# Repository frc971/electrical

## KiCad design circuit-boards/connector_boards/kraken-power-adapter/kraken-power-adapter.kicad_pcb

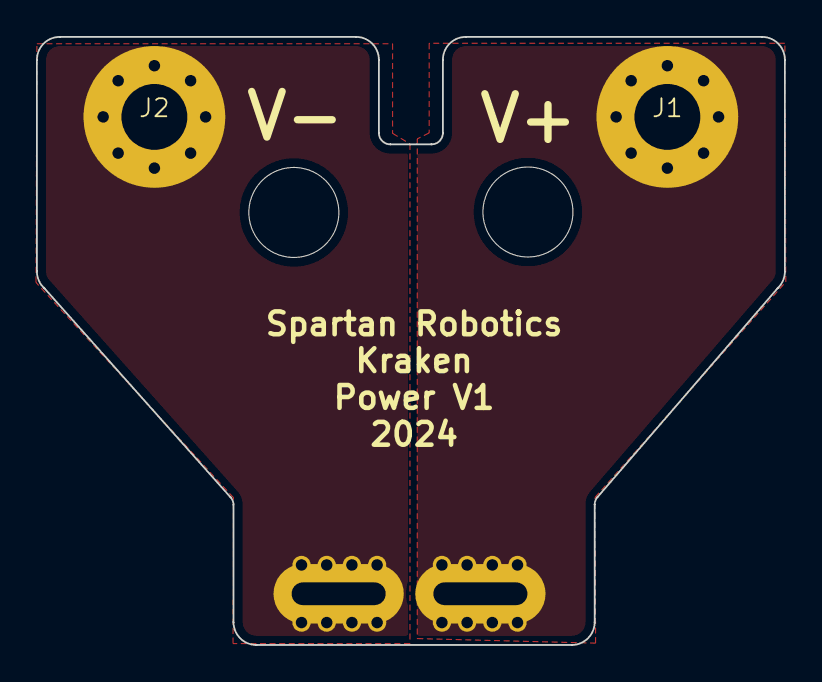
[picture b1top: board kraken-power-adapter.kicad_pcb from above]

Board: 4 copper layers, 41.6 x 33.8 mm, 5 parts (1 on the bottom side), 2 nets.

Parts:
H1, H2: CAN Screw Clearance Hole; MountingHole_5mm
J1: Vbat+; ScrewTerminal-#6
J2: Vbat-; ScrewTerminal-#6
J3: Vbat PP15-45; Dual-side-by-side-1335G1

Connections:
/Vbat+: J1.1, J3.2
/Vbat-: J2.1, J3.1

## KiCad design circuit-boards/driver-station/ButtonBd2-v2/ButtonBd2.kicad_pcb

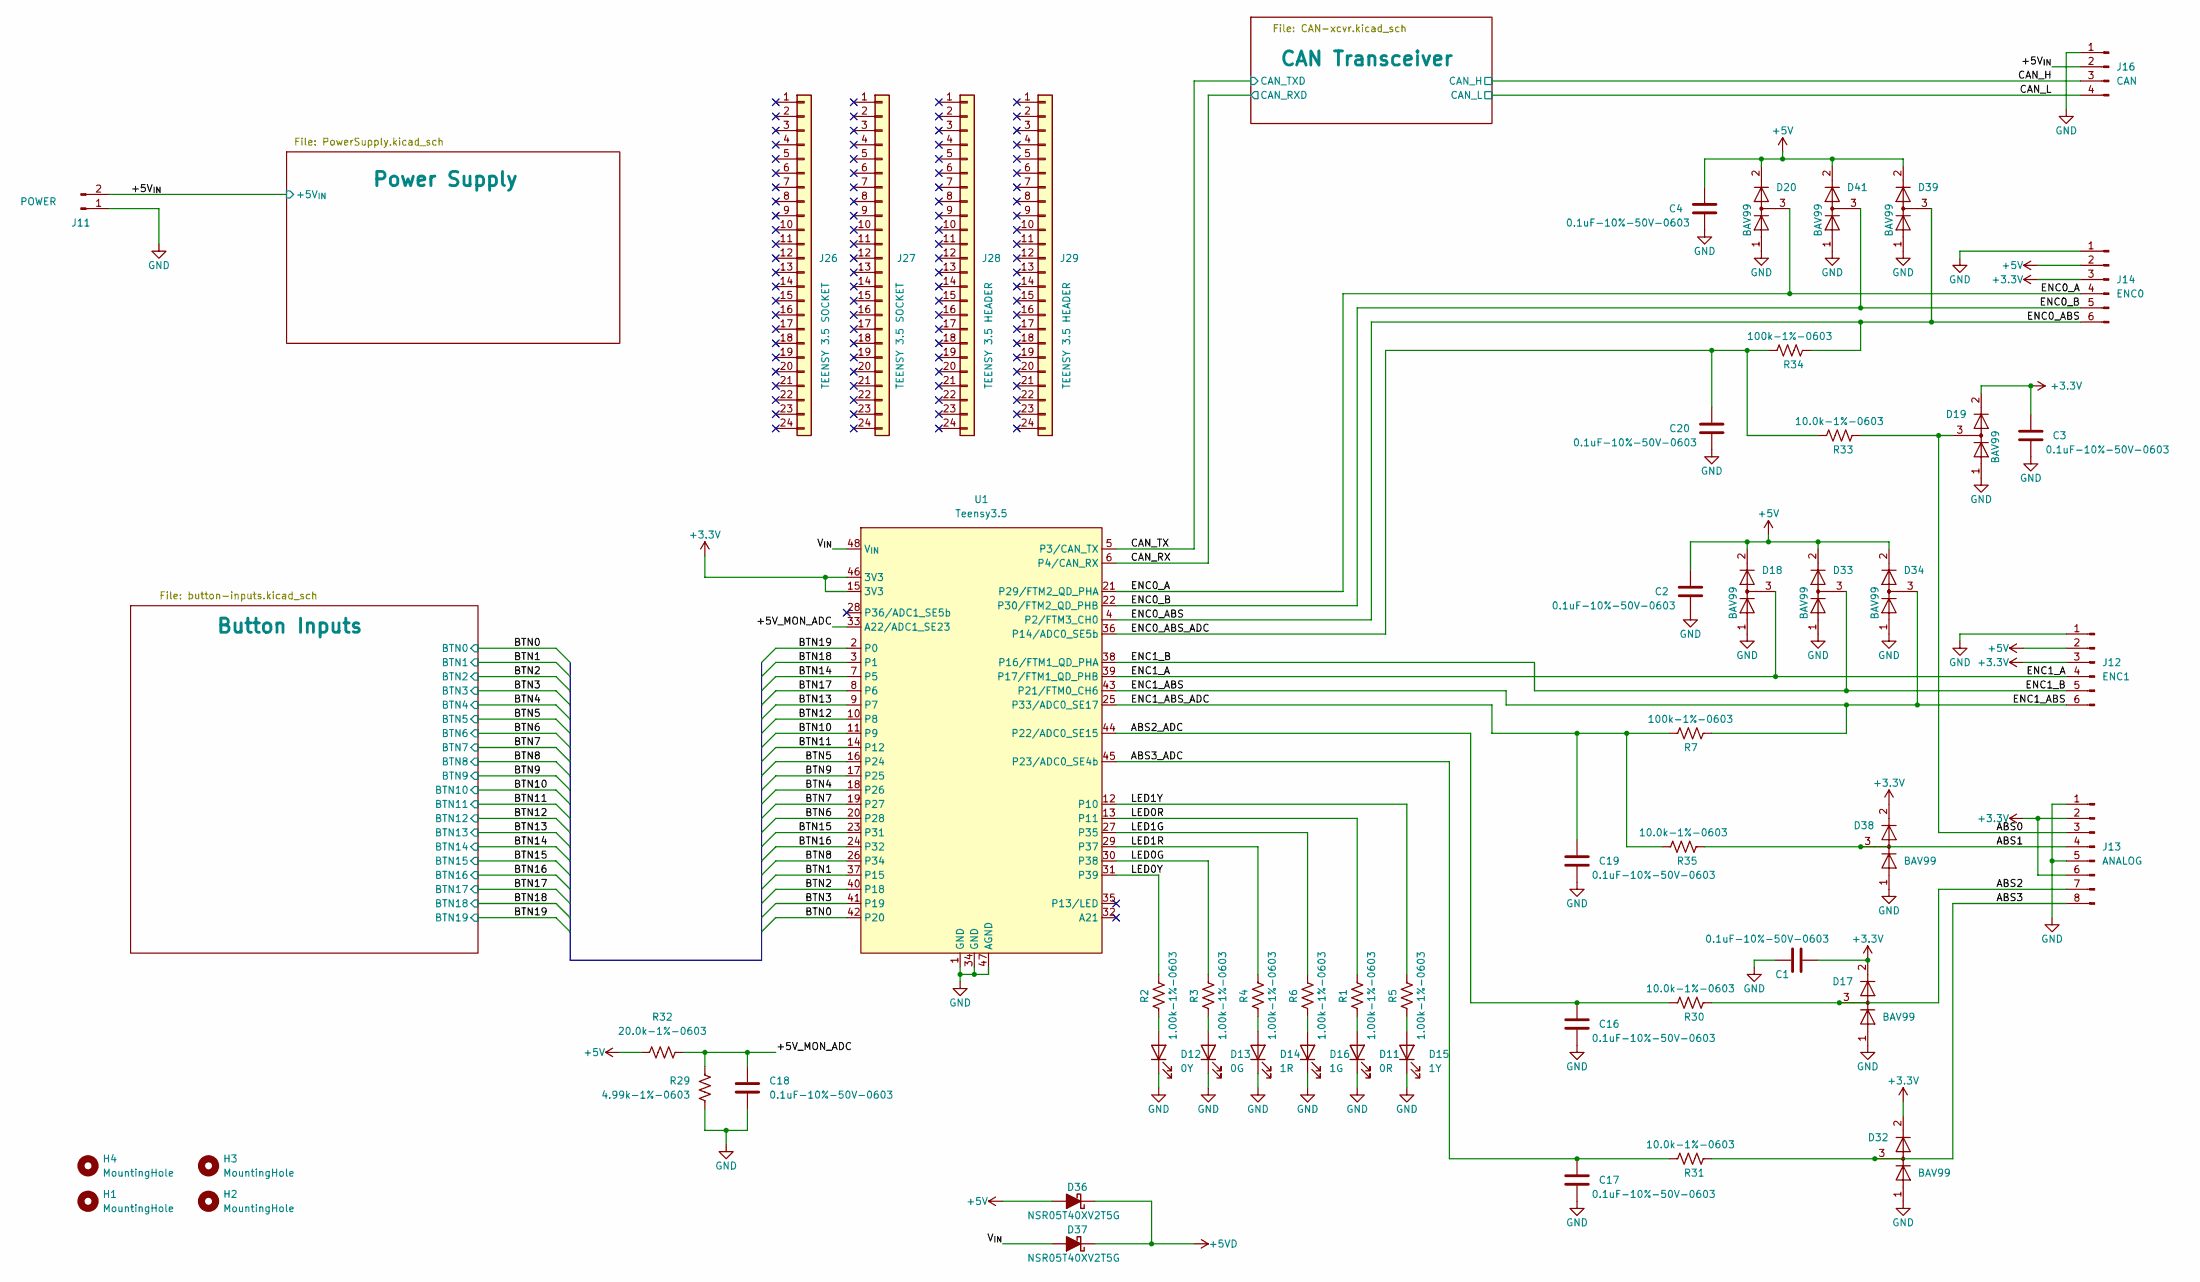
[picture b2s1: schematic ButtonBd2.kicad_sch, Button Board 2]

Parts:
C1, C2, C3, C4, C16, C17, C18, C19, C20: 0.1uF-10%-50V-0603; C_0603_1608Metric; MFG P/N CL10B104KB8NNNC
D11: 0R; LED_0603_1608Metric; MFG P/N 150060RS75000
D12: 0Y; LED_0603_1608Metric; MFG P/N 150060YS75000
D13: 0G; LED_0603_1608Metric; MFG P/N 150060GS75000
D14: 1R; LED_0603_1608Metric; MFG P/N 150060RS75000
D15: 1Y; LED_0603_1608Metric; MFG P/N 150060YS75000
D16: 1G; LED_0603_1608Metric; MFG P/N 150060GS75000
D17, D18, D19, D20, D32, D33, D34, D38, D39, D41: BAV99; SOT-23; MFG P/N BAV99,235
D36, D37: NSR05T40XV2T5G; D_SOD-523; MFG P/N BAT54KFILM
H1, H2, H3, H4: MountingHole; MountingHole_3.2mm_M3
J11: POWER; 70543-0001; MFG P/N 0705430001
J12: ENC1; 70543-0005; MFG P/N 0705430005
J13: ANALOG; 70543-0007; MFG P/N 0705430007
J14: ENC0; 70543-0005; MFG P/N 0705430005
J16: CAN; 70543-0003; MFG P/N 0705430003
J26, J27: TEENSY 3.5 SOCKET; MFG P/N PPPC241LFBN-RC
J28, J29: TEENSY 3.5 HEADER; MFG P/N 0022284245
R1, R2, R3, R4, R5, R6: 1.00k-1%-0603; R_0603_1608Metric; MFG P/N RNCP0603FTD1K00
R7, R34: 100k-1%-0603; R_0603_1608Metric; MFG P/N RC0603FR-07100KL
R29: 4.99k-1%-0603; R_0603_1608Metric; MFG P/N RMCF0603FT4K99
R30, R31, R33, R35: 10.0k-1%-0603; R_0603_1608Metric; MFG P/N RC0603FR-0710KL
R32: 20.0k-1%-0603; R_0603_1608Metric; MFG P/N RC0603FR-0720KL
U1: Teensy3.5; Teensy-DIP-49_W15.24mm_Socket; MFG P/N TEENSY 3.5

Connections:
+3.3V: C1.2, C3.1, D17.2 (A), D19.2 (A), D32.2 (A), D38.2 (A), J12.3, J13.2, J13.6, J14.3, U1.15 (3V3), U1.46 (3V3); also elsewhere on the board
+5V: C2.1, C4.1, D18.2 (A), D20.2 (A), D33.2 (A), D34.2 (A), D36.2 (A), D39.2 (A), D41.2 (A), J12.2, J14.2, R32.2; also elsewhere on the board
+5VD: D36.1 (K), D37.1 (K); also elsewhere on the board
/+5V_MON_ADC: C18.1, R29.1, R32.1, U1.33 (A22/ADC1_SE23)
/+5V_{IN}: J11.2, J16.2; also elsewhere on the board
/ABS0: D19.3 (K), J13.3, R33.2
/ABS1: D38.3 (K), J13.4, R35.2
/ABS2: D17.3 (K), J13.7, R30.2
/ABS2_ADC: C16.1, R30.1, U1.44 (P22/ADC0_SE15)
/ABS3: D32.3 (K), J13.8, R31.2
/ABS3_ADC: C17.1, R31.1, U1.45 (P23/ADC0_SE4b)
/BTN0: U1.42 (P20); also elsewhere on the board
/BTN1: U1.37 (P15); also elsewhere on the board
/BTN2: U1.40 (P18); also elsewhere on the board
/BTN3: U1.41 (P19); also elsewhere on the board
/BTN4: U1.18 (P26); also elsewhere on the board
/BTN5: U1.16 (P24); also elsewhere on the board
/BTN6: U1.20 (P28); also elsewhere on the board
/BTN7: U1.19 (P27); also elsewhere on the board
/BTN8: U1.26 (P34); also elsewhere on the board
/BTN9: U1.17 (P25); also elsewhere on the board
/BTN10: U1.11 (P9); also elsewhere on the board
/BTN11: U1.14 (P12); also elsewhere on the board
/BTN12: U1.10 (P8); also elsewhere on the board
/BTN13: U1.9 (P7); also elsewhere on the board
/BTN14: U1.7 (P5); also elsewhere on the board
/BTN15: U1.23 (P31); also elsewhere on the board
/BTN16: U1.24 (P32); also elsewhere on the board
/BTN17: U1.8 (P6); also elsewhere on the board
/BTN18: U1.3 (P1); also elsewhere on the board
/BTN19: U1.2 (P0); also elsewhere on the board
/CAN_H: J16.3; also elsewhere on the board
/CAN_L: J16.4; also elsewhere on the board
/CAN_RX: U1.6 (P4/CAN_RX); also elsewhere on the board
/CAN_TX: U1.5 (P3/CAN_TX); also elsewhere on the board
/ENC0_A: D20.3 (K), J14.4, U1.21 (P29/FTM2_QD_PHA)
/ENC0_ABS: D39.3 (K), J14.6, R34.2, U1.4 (P2/FTM3_CH0)
/ENC0_ABS_ADC: C20.1, R33.1, R34.1, U1.36 (P14/ADC0_SE5b)
/ENC0_B: D41.3 (K), J14.5, U1.22 (P30/FTM2_QD_PHB)
/ENC1_A: D18.3 (K), J12.4, U1.39 (P17/FTM1_QD_PHB)
/ENC1_ABS: D34.3 (K), J12.6, R7.2, U1.43 (P21/FTM0_CH6)
/ENC1_ABS_ADC: C19.1, R7.1, R35.1, U1.25 (P33/ADC0_SE17)
/ENC1_B: D33.3 (K), J12.5, U1.38 (P16/FTM1_QD_PHA)
/LED0G: R3.1, U1.30 (P38)
/LED0R: R1.1, U1.13 (P11)
/LED0Y: R2.1, U1.31 (P39)
/LED1G: R6.1, U1.27 (P35)
/LED1R: R4.1, U1.29 (P37)
/LED1Y: R5.1, U1.12 (P10)
/V_{IN}: D37.2 (A), U1.48 (V_{IN})
GND: C1.1, C2.2, C3.2, C4.2, C16.2, C17.2, C18.2, C19.2, C20.2, D11.1 (K), D12.1 (K), D13.1 (K), D14.1 (K), D15.1 (K), D16.1 (K), D17.1 (K), D18.1 (K), D19.1 (K), D20.1 (K), D32.1 (K), D33.1 (K), D34.1 (K), D38.1 (K), D39.1 (K), D41.1 (K), J11.1, J12.1, J13.1, J13.5, J14.1, J16.1, R29.2, U1.1 (GND), U1.34 (GND), U1.47 (AGND); also elsewhere on the board
unnamed: D11.2 (A), R1.2
unnamed: D12.2 (A), R2.2
unnamed: D13.2 (A), R3.2
unnamed: D14.2 (A), R4.2
unnamed: D15.2 (A), R5.2
unnamed: D16.2 (A), R6.2

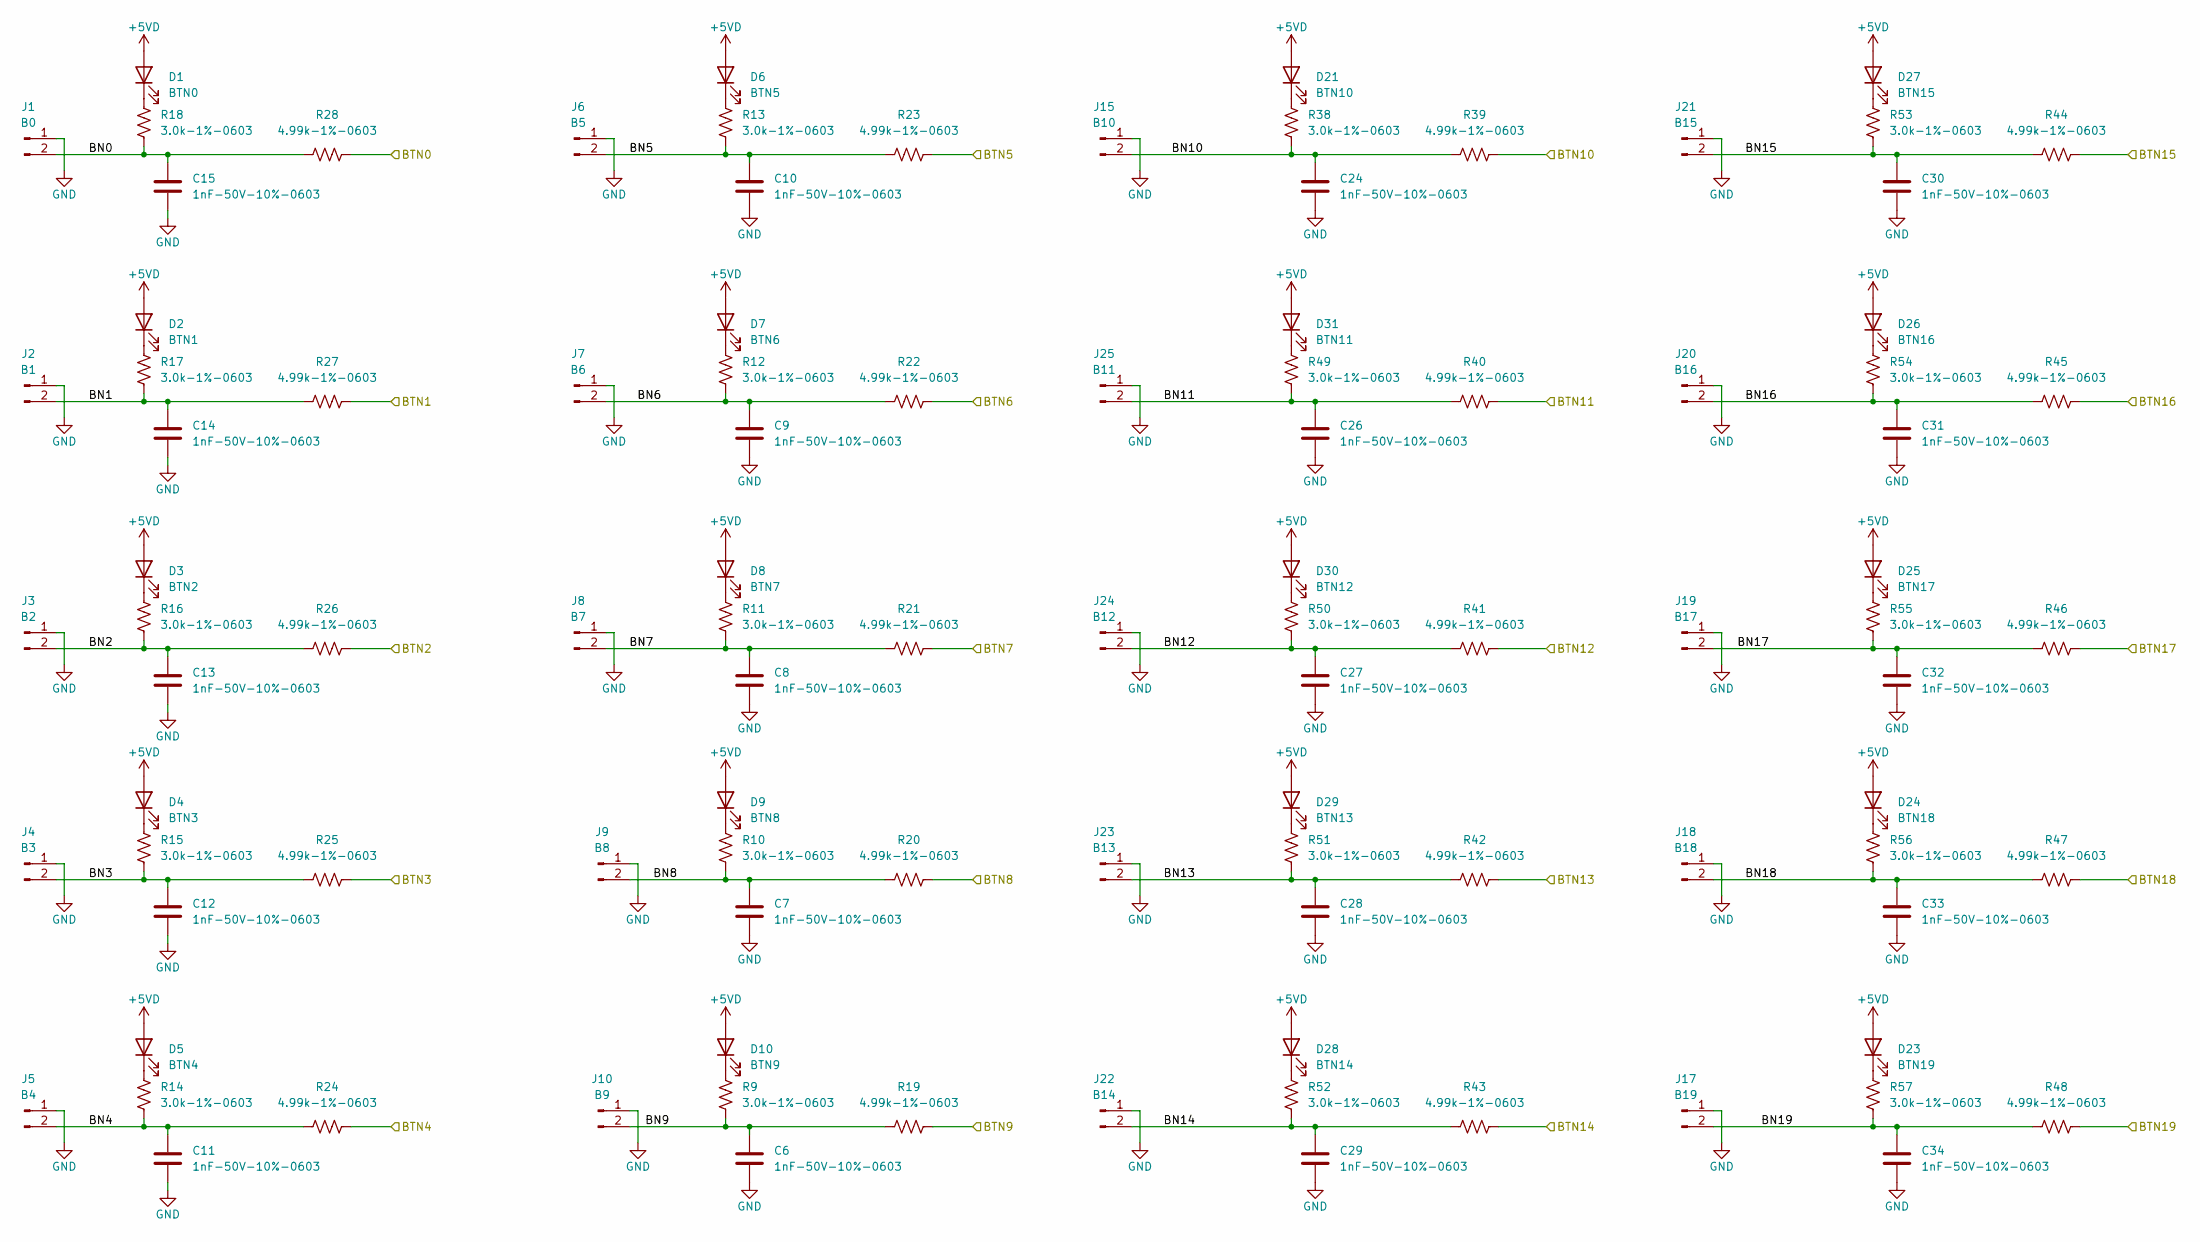
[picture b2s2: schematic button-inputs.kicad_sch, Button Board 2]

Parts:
C6, C7, C8, C9, C10, C11, C12, C13, C14, C15, C24, C26, C27, C28, C29, C30, C31, C32, C33, C34: 1nF-50V-10%-0603; C_0603_1608Metric; MFG P/N CL10B102KB8NNNC
D1: BTN0; LED_0603_1608Metric; MFG P/N 150060YS75000
D2: BTN1; LED_0603_1608Metric; MFG P/N 150060YS75000
D3: BTN2; LED_0603_1608Metric; MFG P/N 150060YS75000
D4: BTN3; LED_0603_1608Metric; MFG P/N 150060YS75000
D5: BTN4; LED_0603_1608Metric; MFG P/N 150060YS75000
D6: BTN5; LED_0603_1608Metric; MFG P/N 150060YS75000
D7: BTN6; LED_0603_1608Metric; MFG P/N 150060YS75000
D8: BTN7; LED_0603_1608Metric; MFG P/N 150060YS75000
D9: BTN8; LED_0603_1608Metric; MFG P/N 150060YS75000
D10: BTN9; LED_0603_1608Metric; MFG P/N 150060YS75000
D21: BTN10; LED_0603_1608Metric; MFG P/N 150060YS75000
D23: BTN19; LED_0603_1608Metric; MFG P/N 150060YS75000
D24: BTN18; LED_0603_1608Metric; MFG P/N 150060YS75000
D25: BTN17; LED_0603_1608Metric; MFG P/N 150060YS75000
D26: BTN16; LED_0603_1608Metric; MFG P/N 150060YS75000
D27: BTN15; LED_0603_1608Metric; MFG P/N 150060YS75000
D28: BTN14; LED_0603_1608Metric; MFG P/N 150060YS75000
D29: BTN13; LED_0603_1608Metric; MFG P/N 150060YS75000
D30: BTN12; LED_0603_1608Metric; MFG P/N 150060YS75000
D31: BTN11; LED_0603_1608Metric; MFG P/N 150060YS75000
J1: B0; 70543-0001; MFG P/N 0705430001
J2: B1; 70543-0001; MFG P/N 0705430001
J3: B2; 70543-0001; MFG P/N 0705430001
J4: B3; 70543-0001; MFG P/N 0705430001
J5: B4; 70543-0001; MFG P/N 0705430001
J6: B5; 70543-0001; MFG P/N 0705430001
J7: B6; 70543-0001; MFG P/N 0705430001
J8: B7; 70543-0001; MFG P/N 0705430001
J9: B8; 70543-0001; MFG P/N 0705430001
J10: B9; 70543-0001; MFG P/N 0705430001
J15: B10; 70543-0001; MFG P/N 0705430001
J17: B19; 70543-0001; MFG P/N 0705430001
J18: B18; 70543-0001; MFG P/N 0705430001
J19: B17; 70543-0001; MFG P/N 0705430001
J20: B16; 70543-0001; MFG P/N 0705430001
J21: B15; 70543-0001; MFG P/N 0705430001
J22: B14; 70543-0001; MFG P/N 0705430001
J23: B13; 70543-0001; MFG P/N 0705430001
J24: B12; 70543-0001; MFG P/N 0705430001
J25: B11; 70543-0001; MFG P/N 0705430001
R9, R10, R11, R12, R13, R14, R15, R16, R17, R18, R38, R49, R50, R51, R52, R53, R54, R55, R56, R57: 3.0k-1%-0603; R_0603_1608Metric; MFG P/N RC0603FR-073KL
R19, R20, R21, R22, R23, R24, R25, R26, R27, R28, R39, R40, R41, R42, R43, R44, R45, R46, R47, R48: 4.99k-1%-0603; R_0603_1608Metric; MFG P/N RMCF0603FT4K99

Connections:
+5VD: D1.2 (A), D2.2 (A), D3.2 (A), D4.2 (A), D5.2 (A), D6.2 (A), D7.2 (A), D8.2 (A), D9.2 (A), D10.2 (A), D21.2 (A), D23.2 (A), D24.2 (A), D25.2 (A), D26.2 (A), D27.2 (A), D28.2 (A), D29.2 (A), D30.2 (A), D31.2 (A); also elsewhere on the board
/BTN0: R28.2; also elsewhere on the board
/BTN1: R27.2; also elsewhere on the board
/BTN2: R26.2; also elsewhere on the board
/BTN3: R25.2; also elsewhere on the board
/BTN4: R24.2; also elsewhere on the board
/BTN5: R23.2; also elsewhere on the board
/BTN6: R22.2; also elsewhere on the board
/BTN7: R21.2; also elsewhere on the board
/BTN8: R20.2; also elsewhere on the board
/BTN9: R19.2; also elsewhere on the board
/BTN10: R39.2; also elsewhere on the board
/BTN11: R40.2; also elsewhere on the board
/BTN12: R41.2; also elsewhere on the board
/BTN13: R42.2; also elsewhere on the board
/BTN14: R43.2; also elsewhere on the board
/BTN15: R44.2; also elsewhere on the board
/BTN16: R45.2; also elsewhere on the board
/BTN17: R46.2; also elsewhere on the board
/BTN18: R47.2; also elsewhere on the board
/BTN19: R48.2; also elsewhere on the board
/Button Inputs/BN0: C15.1, J1.2, R18.2, R28.1
/Button Inputs/BN1: C14.1, J2.2, R17.2, R27.1
/Button Inputs/BN2: C13.1, J3.2, R16.2, R26.1
/Button Inputs/BN3: C12.1, J4.2, R15.2, R25.1
/Button Inputs/BN4: C11.1, J5.2, R14.2, R24.1
/Button Inputs/BN5: C10.1, J6.2, R13.2, R23.1
/Button Inputs/BN6: C9.1, J7.2, R12.2, R22.1
/Button Inputs/BN7: C8.1, J8.2, R11.2, R21.1
/Button Inputs/BN8: C7.1, J9.2, R10.2, R20.1
/Button Inputs/BN9: C6.1, J10.2, R9.2, R19.1
/Button Inputs/BN10: C24.1, J15.2, R38.2, R39.1
/Button Inputs/BN11: C26.1, J25.2, R40.1, R49.2
/Button Inputs/BN12: C27.1, J24.2, R41.1, R50.2
/Button Inputs/BN13: C28.1, J23.2, R42.1, R51.2
/Button Inputs/BN14: C29.1, J22.2, R43.1, R52.2
/Button Inputs/BN15: C30.1, J21.2, R44.1, R53.2
/Button Inputs/BN16: C31.1, J20.2, R45.1, R54.2
/Button Inputs/BN17: C32.1, J19.2, R46.1, R55.2
/Button Inputs/BN18: C33.1, J18.2, R47.1, R56.2
/Button Inputs/BN19: C34.1, J17.2, R48.1, R57.2
GND: C6.2, C7.2, C8.2, C9.2, C10.2, C11.2, C12.2, C13.2, C14.2, C15.2, C24.2, C26.2, C27.2, C28.2, C29.2, C30.2, C31.2, C32.2, C33.2, C34.2, J1.1, J2.1, J3.1, J4.1, J5.1, J6.1, J7.1, J8.1, J9.1, J10.1, J15.1, J17.1, J18.1, J19.1, J20.1, J21.1, J22.1, J23.1, J24.1, J25.1; also elsewhere on the board
unnamed: D1.1 (K), R18.1
unnamed: D2.1 (K), R17.1
unnamed: D3.1 (K), R16.1
unnamed: D4.1 (K), R15.1
unnamed: D5.1 (K), R14.1
unnamed: D6.1 (K), R13.1
unnamed: D7.1 (K), R12.1
unnamed: D8.1 (K), R11.1
unnamed: D9.1 (K), R10.1
unnamed: D10.1 (K), R9.1
unnamed: D21.1 (K), R38.1
unnamed: D23.1 (K), R57.1
unnamed: D24.1 (K), R56.1
unnamed: D25.1 (K), R55.1
unnamed: D26.1 (K), R54.1
unnamed: D27.1 (K), R53.1
unnamed: D28.1 (K), R52.1
unnamed: D29.1 (K), R51.1
unnamed: D30.1 (K), R50.1
unnamed: D31.1 (K), R49.1

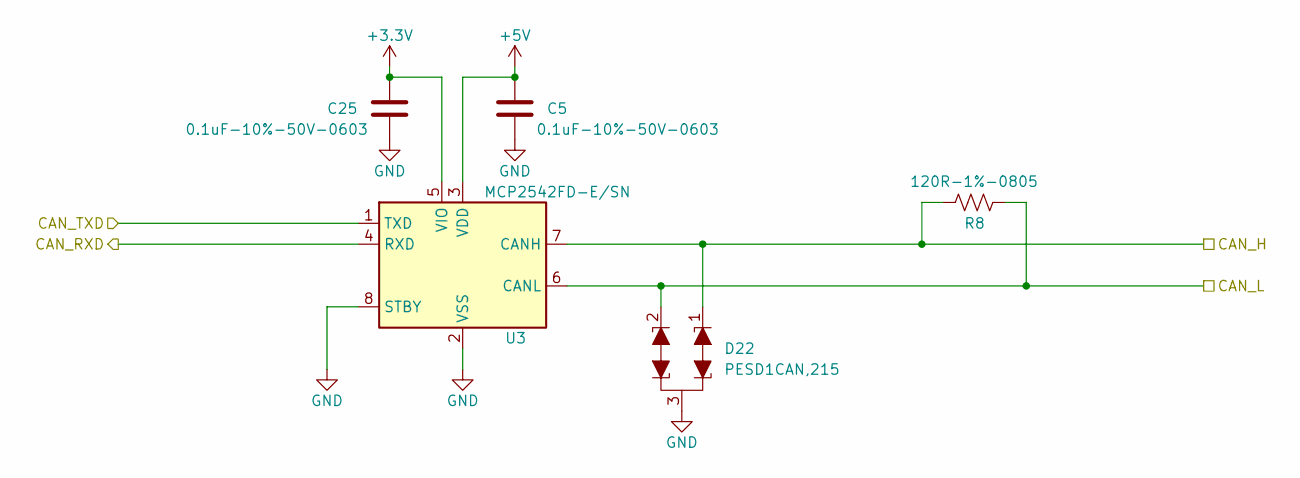
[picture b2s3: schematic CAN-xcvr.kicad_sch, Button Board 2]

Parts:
C5, C25: 0.1uF-10%-50V-0603; C_0603_1608Metric; MFG P/N CL10B104KB8NNNC
D22: PESD1CAN; SOT-23; MFG P/N PESD1CAN,215
R8: 120R-1%-0805; R_0805_2012Metric; MFG P/N RMCF0805FT120R
U3: MCP2542FD-E/SN; SO-8_3.9x4.9mm_P1.27mm; MFG P/N MCP2542FD-E/SN

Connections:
+3.3V: C25.1, U3.5 (VIO); also elsewhere on the board
+5V: C5.1, U3.3 (VDD); also elsewhere on the board
/CAN_H: D22.1 (K1), R8.1, U3.7 (CANH); also elsewhere on the board
/CAN_L: D22.2 (K1), R8.2, U3.6 (CANL); also elsewhere on the board
/CAN_RX: U3.4 (RXD); also elsewhere on the board
/CAN_TX: U3.1 (TXD); also elsewhere on the board
GND: C5.2, C25.2, D22.3 (KK), U3.2 (VSS), U3.8 (STBY); also elsewhere on the board

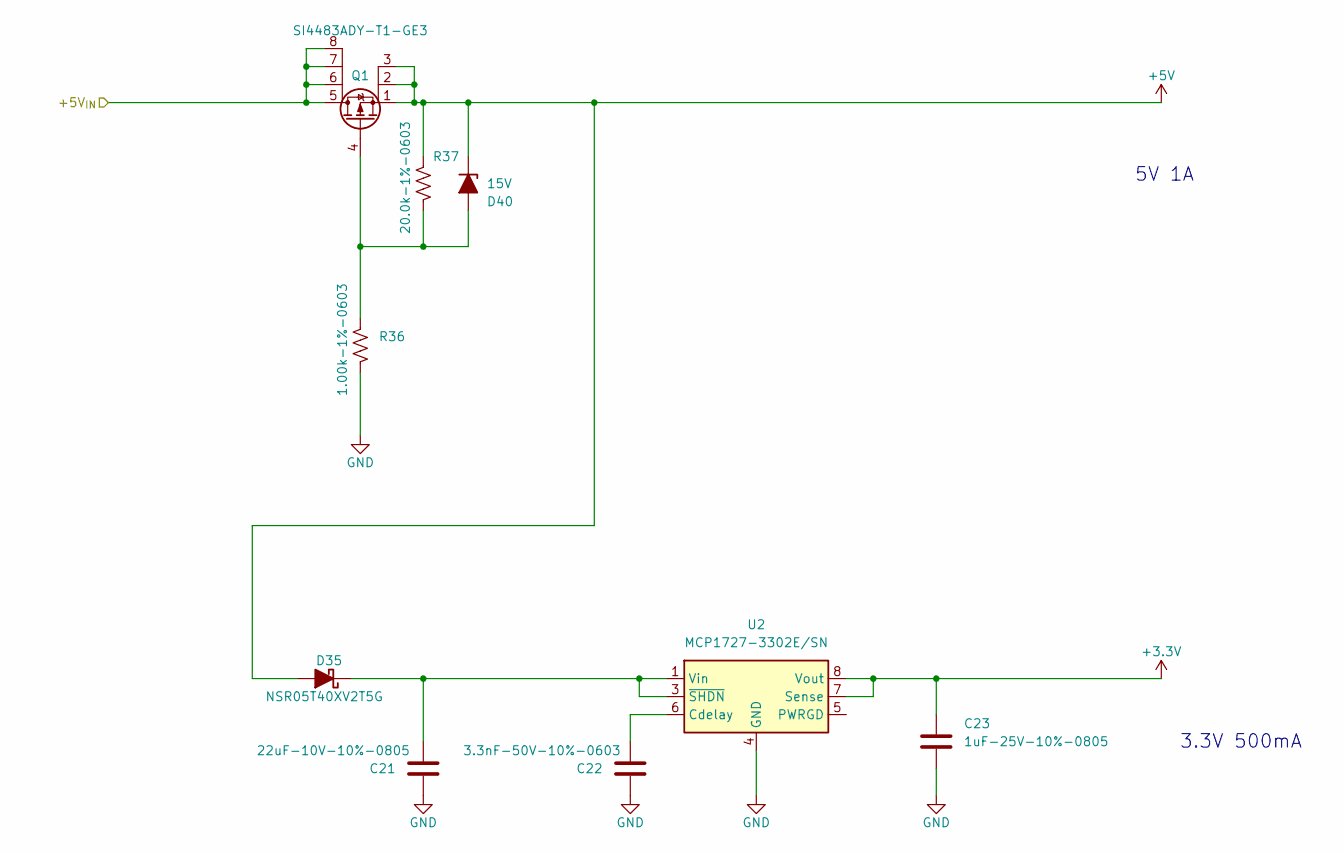
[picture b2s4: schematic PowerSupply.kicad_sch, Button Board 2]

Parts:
C21: 22uF-10V-10%-0805; C_0805_2012Metric; MFG P/N CL21A226KPCLRNC
C22: 3.3nF-50V-10%-0603; C_0603_1608Metric; MFG P/N CL10B332KB8NNNC
C23: 1uF-25V-10%-0805; C_0805_2012Metric; MFG P/N CL21B105KAFNNNE
D35: NSR05T40XV2T5G; D_SOD-523; MFG P/N BAT54KFILM
D40: 15V; D_SOD-123F; MFG P/N BZT52H-C15,115
Q1: SI4483ADY-T1-GE3; SOIC-8_3.9x4.9mm_P1.27mm; MFG P/N SI4483ADY-T1-GE3
R36: 1.00k-1%-0603; R_0603_1608Metric; MFG P/N RNCP0603FTD1K00
R37: 20.0k-1%-0603; R_0603_1608Metric; MFG P/N RC0603FR-0720KL
U2: MCP1727-3302E/SN; SOIC-8_3.9x4.9mm_P1.27mm; MFG P/N MCP1727-3302E/SN

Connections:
+3.3V: C23.1, U2.7 (Sense), U2.8 (Vout); also elsewhere on the board
+5V: D35.2 (A), D40.1 (K), Q1.1 (S), Q1.2 (S), Q1.3 (S), R37.2; also elsewhere on the board
/+5V_{IN}: Q1.5 (D), Q1.6 (D), Q1.7 (D), Q1.8 (D); also elsewhere on the board
GND: C21.2, C22.2, C23.2, R36.1, U2.4 (GND); also elsewhere on the board
unnamed: C21.1, D35.1 (K), U2.1 (Vin), U2.2 (Vin), U2.3 (~SHDN)
unnamed: D40.2 (A), Q1.4 (G), R36.2, R37.1
unnamed: C22.1, U2.6 (Cdelay)

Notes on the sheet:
3.3V 500mA
5V 1A

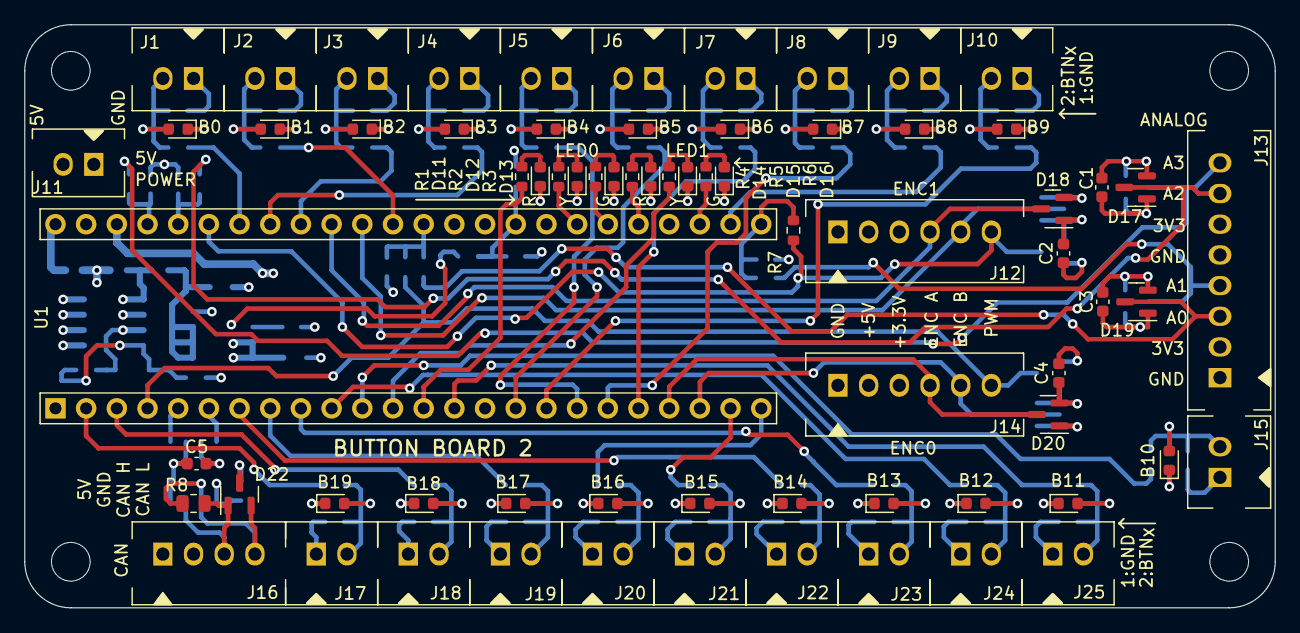
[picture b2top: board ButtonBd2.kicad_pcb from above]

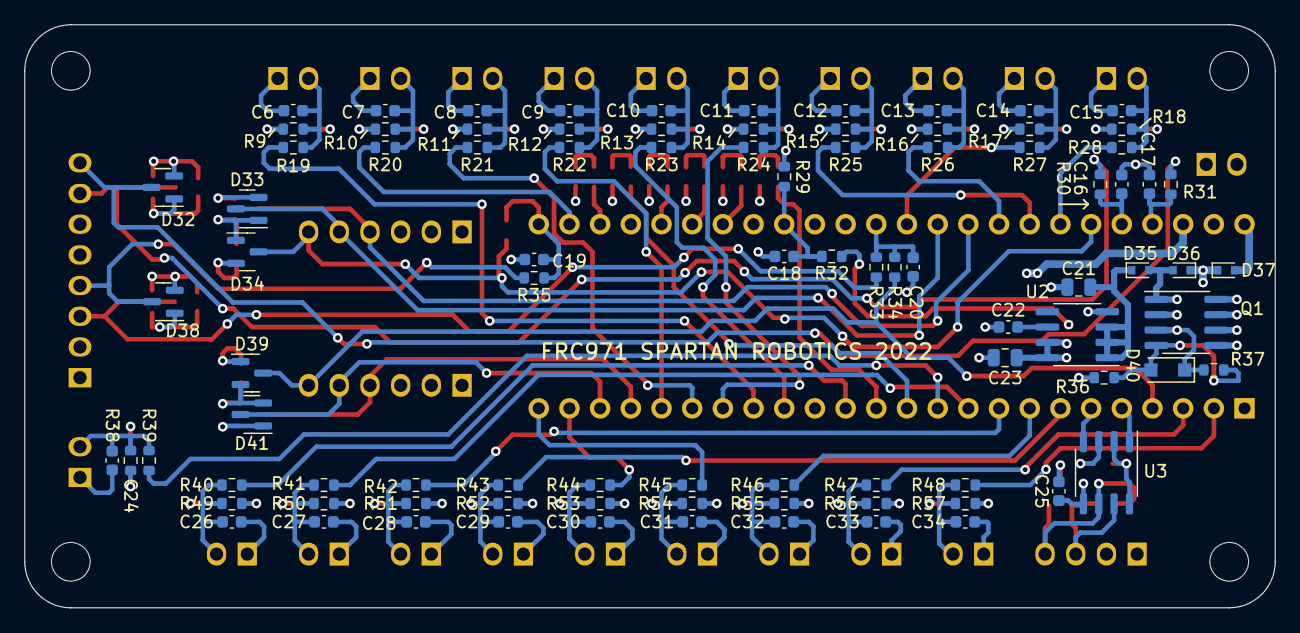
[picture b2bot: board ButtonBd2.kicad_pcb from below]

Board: 4 copper layers, 103.5 x 48.3 mm, 165 parts (91 on the bottom side), 100 nets.

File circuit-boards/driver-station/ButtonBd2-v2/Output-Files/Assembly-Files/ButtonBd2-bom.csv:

Item,QUANTITY,Reference,Value,MFG,MFG P/N,DIST,DIST P/N
1,1,C21,22uF-10V-10%-0805,Samsung Electro-Mechanics,CL21A226KPCLRNC,Digikey,1276-6786-1-ND
2,1,C22,3.3nF-50V-10%-0603,Samsung Electro-Mechanics,CL10B332KB8NNNC,Digikey,1276-1758-1-ND
3,1,C23,1uF-25V-10%-0805,Samsung Electro-Mechanics,CL21B105KAFNNNE,Digikey,1276-1066-1-ND
4,11,"C1-C5,C16-C20,C25",0.1uF-10%-50V-0603,Samsung Electro-Mechanics,CL10B104KB8NNNC,Digikey,1276-1000-1-ND
5,20,"C6-C15,C24,C26-C34",1nF-50V-10%-0603,Samsung Electro-Mechanics,CL10B102KB8NNNC,Digikey,1276-1018-1-ND
6,1,D22,PESD1CAN,Nexperia,"PESD1CAN,215",Digikey,1727-3817-1-ND
7,1,D40,15V,Nexperia,"BZT52H-C15,115",Digikey,1727-3593-1-ND
8,22,"D1-D10,D12,D15,D21,D23-D31",-- mixed values --,Wurth Electronik,150060YS75000,Digikey,732-4981-1-ND
9,2,"D11,D14",-- mixed values --,Wurth Electronik,150060RS75000,Digikey,732-4978-1-ND
10,2,"D13,D16",-- mixed values --,Wurth Electronik,150060GS75000,Digikey,732-4971-1-ND
11,10,"D17-D20,D32-D34,D38,D39,D41",BAV99,Nexperia USA Inc.,"BAV99,235",Digikey,1727-4311-1-ND
12,3,D35-D37,NSR05T40XV2T5G,STMicroelectronics,BAT54KFILM,Digikey,497-5561-1-ND
13,1,J13,ANALOG,Molex,705430007,Digikey,WM4806-ND
14,1,J16,CAN,Molex,705430003,Digikey,WM4802-ND
15,21,"J1-J11,J15,J17-J25",-- mixed values --,Molex,705430001,Digikey,WM4800-ND
16,2,"J12,J14",-- mixed values --,Molex,705430005,Digikey,WM4804-ND
17,2,"J26,J27",TEENSY 3.5 SOCKET,Sullins,PPPC241LFBN-RC,Digikey,S7057-ND
18,2,"J28,J29",TEENSY 3.5 HEADER,Molex,22284245,Digikey,900-0022284245-ND
19,1,Q1,SI4483ADY-T1-GE3,Vishay,SI4483ADY-T1-GE3,Digikey,SI4483ADY-T1-GE3CT-ND
20,1,R8,120R-1%-0805,Stackpole Electronics Inc,RMCF0805FT120R,Digikey,738-RMCF0805FT120RCT-ND
21,7,"R1-R6,R36",1.00k-1%-0603,Stackpole Electronics Inc,RNCP0603FTD1K00,Digikey,RNCP0603FTD1K00CT-ND
22,21,"R19-R29,R39-R48",4.99k-1%-0603,Stackpole Electronics Inc,RMCF0603FT4K99,Digikey,RMCF0603FT4K99CT-ND
23,4,"R30,R31,R33,R35",10.0k-1%-0603,YAGEO,RC0603FR-0710KL,Digikey,311-10.0KHRCT-ND
24,2,"R32,R37",20.0k-1%-0603,YAGEO,RC0603FR-0720KL,Digikey,311-20.0KHRCT-ND
25,2,"R7,R34",100k-1%-0603,YAGEO,RC0603FR-07100KL,Digikey,311-100KHRCT-ND
26,20,"R9-R18,R38,R49-R57",3.0k-1%-0603,YAGEO,RC0603FR-073KL,Digikey,311-3.00KHRCT-ND
27,1,U1,Teensy3.5,PJRC,TEENSY 3.5,,
28,1,U2,MCP1727-3302E/SN,Microchip,MCP1727-3302E/SN,Digikey,MCP1727-3302E/SN-ND
29,1,U3,MCP2542FD-E/SN,Microchip,MCP2542FD-E/SN,Digikey,MCP2542FD-E/SN-ND

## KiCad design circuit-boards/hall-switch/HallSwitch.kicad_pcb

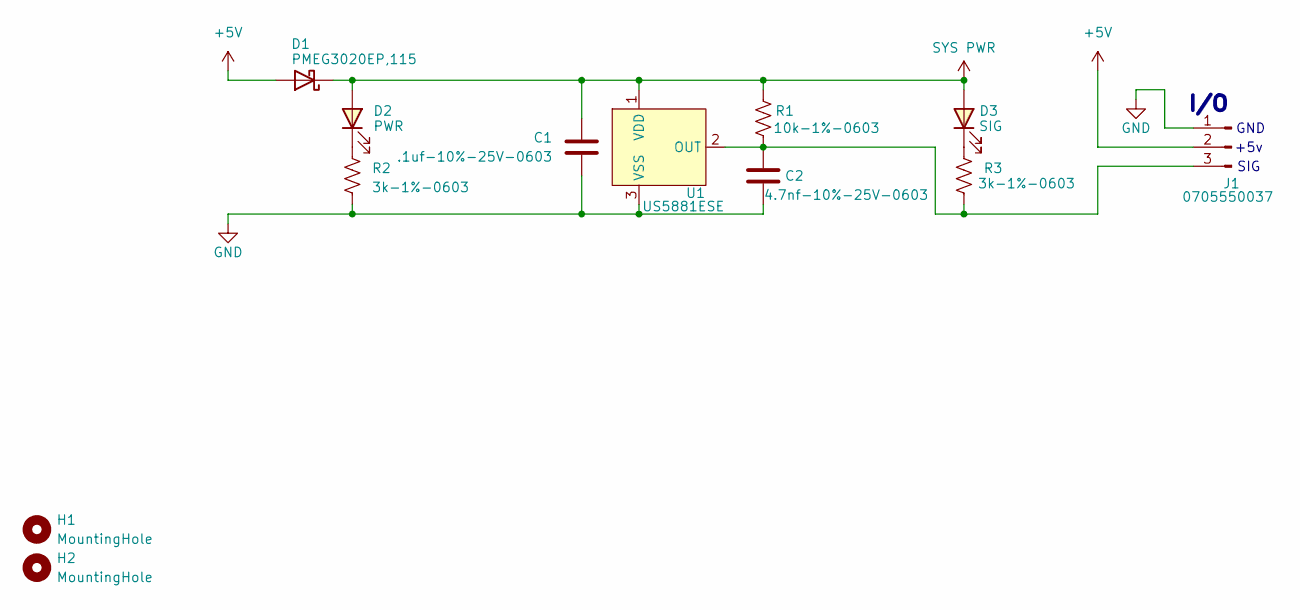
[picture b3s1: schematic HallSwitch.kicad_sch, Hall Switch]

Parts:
C1: .1uf-10%-25V-0603; C_0603_1608Metric; MFG P/N C0603C104K3RAC7867
C2: 4.7nf-10%-25V-0603; C_0603_1608Metric; MFG P/N C0603C472K3RAC7867
D1: PMEG3020EP,115; D_SOD-128; MFG P/N 1727-5836-1-ND
D2: PWR; LED_0603_1608Metric; MFG P/N SML-LXFT0603GC-TR
D3: SIG; LED_0603_1608Metric; MFG P/N SML-LXFT0603GC-TR
H1, H2: MountingHole; MountingHole_2.1mm
J1: 0705550037; 70555-0037; MFG P/N 0705550037
R1: 10k-1%-0603; R_0603_1608Metric; MFG P/N RC0603FR-0710KL
R2, R3: 3k-1%-0603; R_0603_1608Metric; MFG P/N ERA-3AEB302VRMCF0603FT3K00
U1: US5881ESE; SOT-23-3; MFG P/N US5881ESE-AAA-000-RECT-ND

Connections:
+5V: D1.2 (A), J1.2
GND: C1.2, C2.2, J1.1, R2.2, U1.3 (VSS)
unnamed: D2.1 (K), R2.1
unnamed: D3.1 (K), R3.1
unnamed: C2.1, J1.3, R1.2, R3.2, U1.2 (OUT)
SYS PWR: C1.1, D1.1 (K), D2.2 (A), D3.2 (A), R1.1, U1.1 (VDD)

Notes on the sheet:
GND
SIG
I/O
+5v

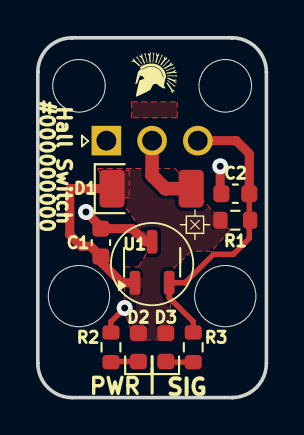
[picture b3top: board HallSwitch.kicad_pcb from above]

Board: 2 copper layers, 12.7 x 20.0 mm, 12 parts (1 on the bottom side), 6 nets.

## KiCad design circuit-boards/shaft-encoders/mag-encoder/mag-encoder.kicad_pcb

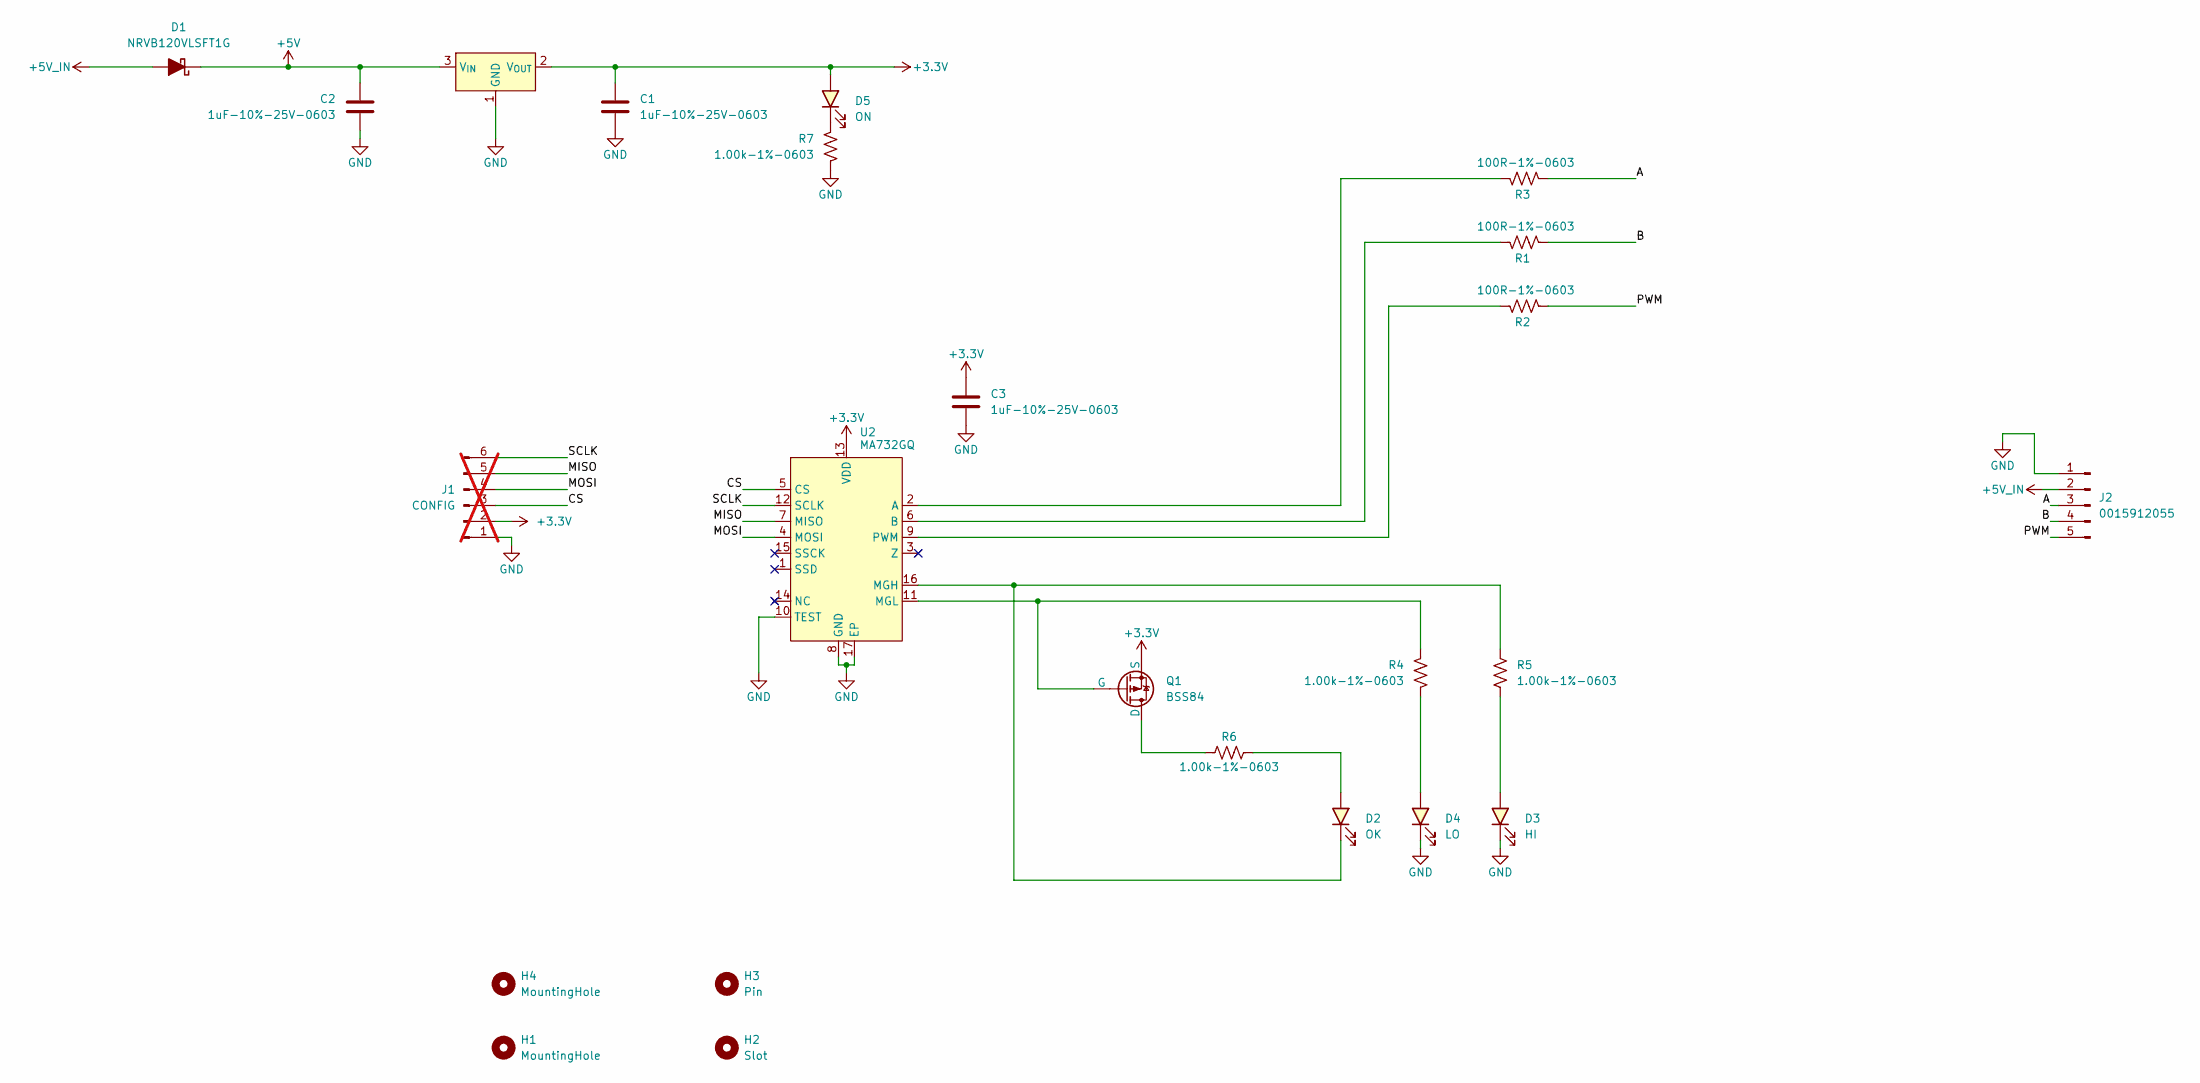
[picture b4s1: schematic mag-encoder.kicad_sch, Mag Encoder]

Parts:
C1, C2, C3: 1uF-10%-25V-0603; C_0603_1608Metric; MFG P/N 06033C105KAT2A
D1: NRVB120VLSFT1G; D_SOD-123F; MFG P/N NRVB120VLSFT1G
D2: OK; LED_0603_1608Metric; MFG P/N 150060GS75000
D3: HI; LED_0603_1608Metric; MFG P/N 150060RS75000
D4: LO; LED_0603_1608Metric; MFG P/N 150060RS75000
D5: ON; LED_0603_1608Metric; MFG P/N 150060GS75000
H1, H4: MountingHole; MountingHole_3.2mm_M3
H2: Slot; pin-0.100
H3: Pin; pin-0.100
J1: CONFIG; PinHeader_1x06_P2.54mm_Vertical; not fitted
J2: 0015912055; Molex-70634-0039; MFG P/N 0015912055
Q1: BSS84; SOT-23; MFG P/N BSS84
R1, R2, R3: 100R-1%-0603; R_0603_1608Metric; MFG P/N RC0603FR-07100RL
R4, R5, R6, R7: 1.00k-1%-0603; R_0603_1608Metric; MFG P/N RC0603FR-071KL
U1: AP2120N-3.3TRG1; SOT-23; MFG P/N AP2120N-3.3TRG1
U2: MA732GQ; QFN-16-1EP_3x3mm_P0.5mm_EP1.7x1.7mm; MFG P/N MA732GQ-Z

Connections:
+3.3V: C1.1, C3.1, D5.2 (A), J1.2, Q1.2 (S), U1.2 (V_{OUT}), U2.13 (VDD)
+5V: C2.1, D1.1 (K), U1.3 (V_{IN})
+5V_IN: D1.2 (A), J2.2
/A: J2.3, R3.2
/B: J2.4, R1.2
/CS: J1.3, U2.5 (CS)
/MISO: J1.5, U2.7 (MISO)
/MOSI: J1.4, U2.4 (MOSI)
/PWM: J2.5, R2.2
/SCLK: J1.6, U2.12 (SCLK)
GND: C1.2, C2.2, C3.2, D3.1 (K), D4.1 (K), J1.1, J2.1, R7.2, U1.1 (GND), U2.8 (GND), U2.10 (TEST), U2.17 (EP)
unnamed: D2.2 (A), R6.2
unnamed: D2.1 (K), R5.1, U2.16 (MGH)
unnamed: D3.2 (A), R5.2
unnamed: D4.2 (A), R4.2
unnamed: D5.1 (K), R7.1
unnamed: Q1.3 (D), R6.1
unnamed: Q1.1 (G), R4.1, U2.11 (MGL)
unnamed: R3.1, U2.2 (A)
unnamed: R1.1, U2.6 (B)
unnamed: R2.1, U2.9 (PWM)

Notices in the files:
parts and their libraries:
Copyright 2021 Accelerated Designs. All rights reserved.
